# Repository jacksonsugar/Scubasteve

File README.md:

# Scubasteve
Files and notes for AUV development

Microstrain driver

http://wiki.ros.org/microstrain_3dm_gx5_45

https://github.com/sjphilli/microstrain_3dm_gx5_45

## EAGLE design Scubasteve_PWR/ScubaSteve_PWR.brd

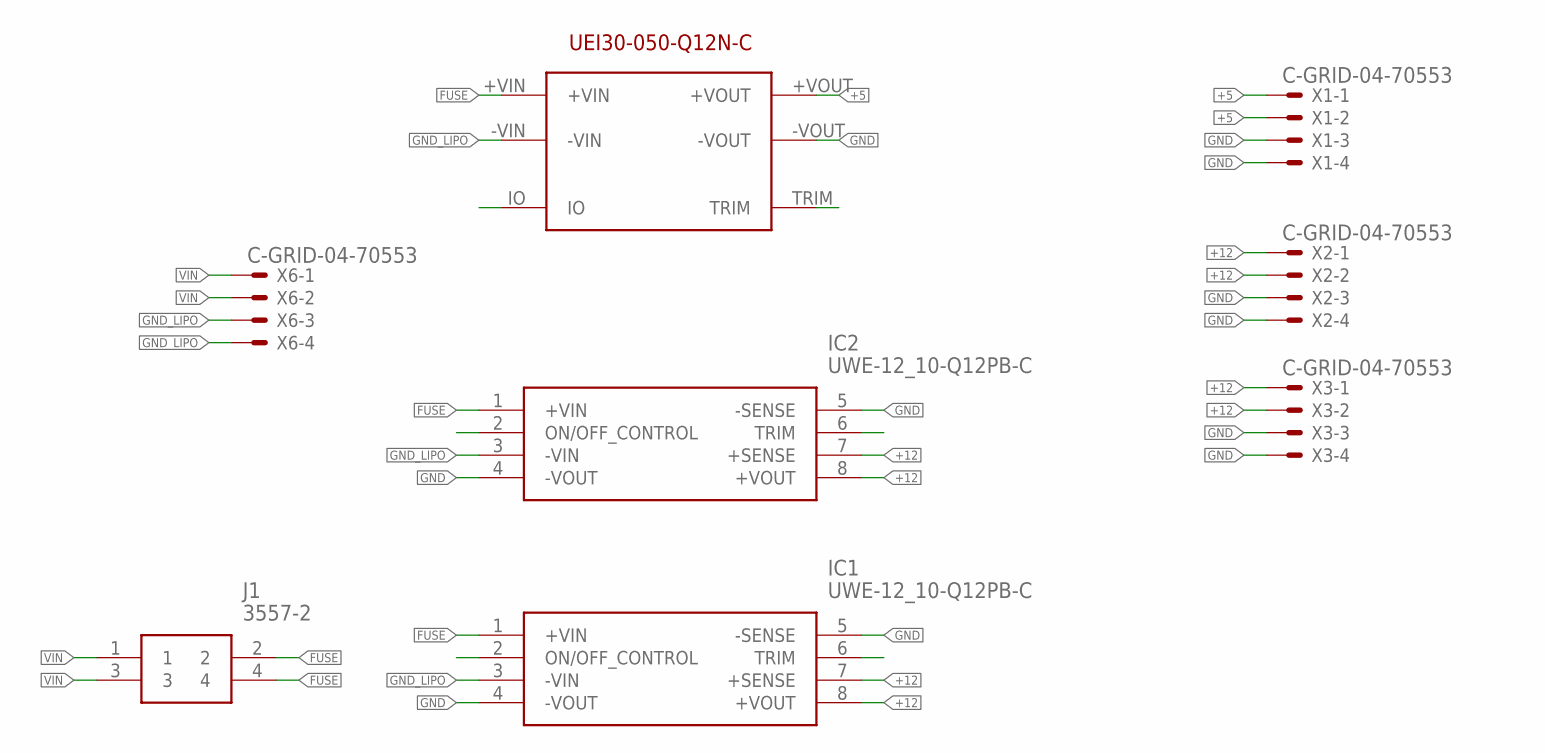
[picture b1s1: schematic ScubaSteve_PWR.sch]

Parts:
IC1, IC2: UWE-12_10-Q12PB-C; UWE520Q48NC
J1: 3557-2
U$1: UEI30-050-Q12N-C
X1, X2, X3, X6: C-GRID-04-70553; 70553-04

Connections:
+5: U$1.+VOUT, X1.1, X1.2
+12: IC1.7 (+SENSE), IC1.8 (+VOUT), IC2.7 (+SENSE), IC2.8 (+VOUT), X2.1, X2.2, X3.1, X3.2
FUSE: IC1.1 (+VIN), IC2.1 (+VIN), J1.2, J1.4, U$1.+VIN
GND: IC1.4 (-VOUT), IC1.5 (-SENSE), IC2.4 (-VOUT), IC2.5 (-SENSE), U$1.-VOUT, X1.3, X1.4, X2.3, X2.4, X3.3, X3.4
GND_LIPO: IC1.3 (-VIN), IC2.3 (-VIN), U$1.-VIN, X6.3, X6.4
VIN: J1.1, J1.3, X6.1, X6.2

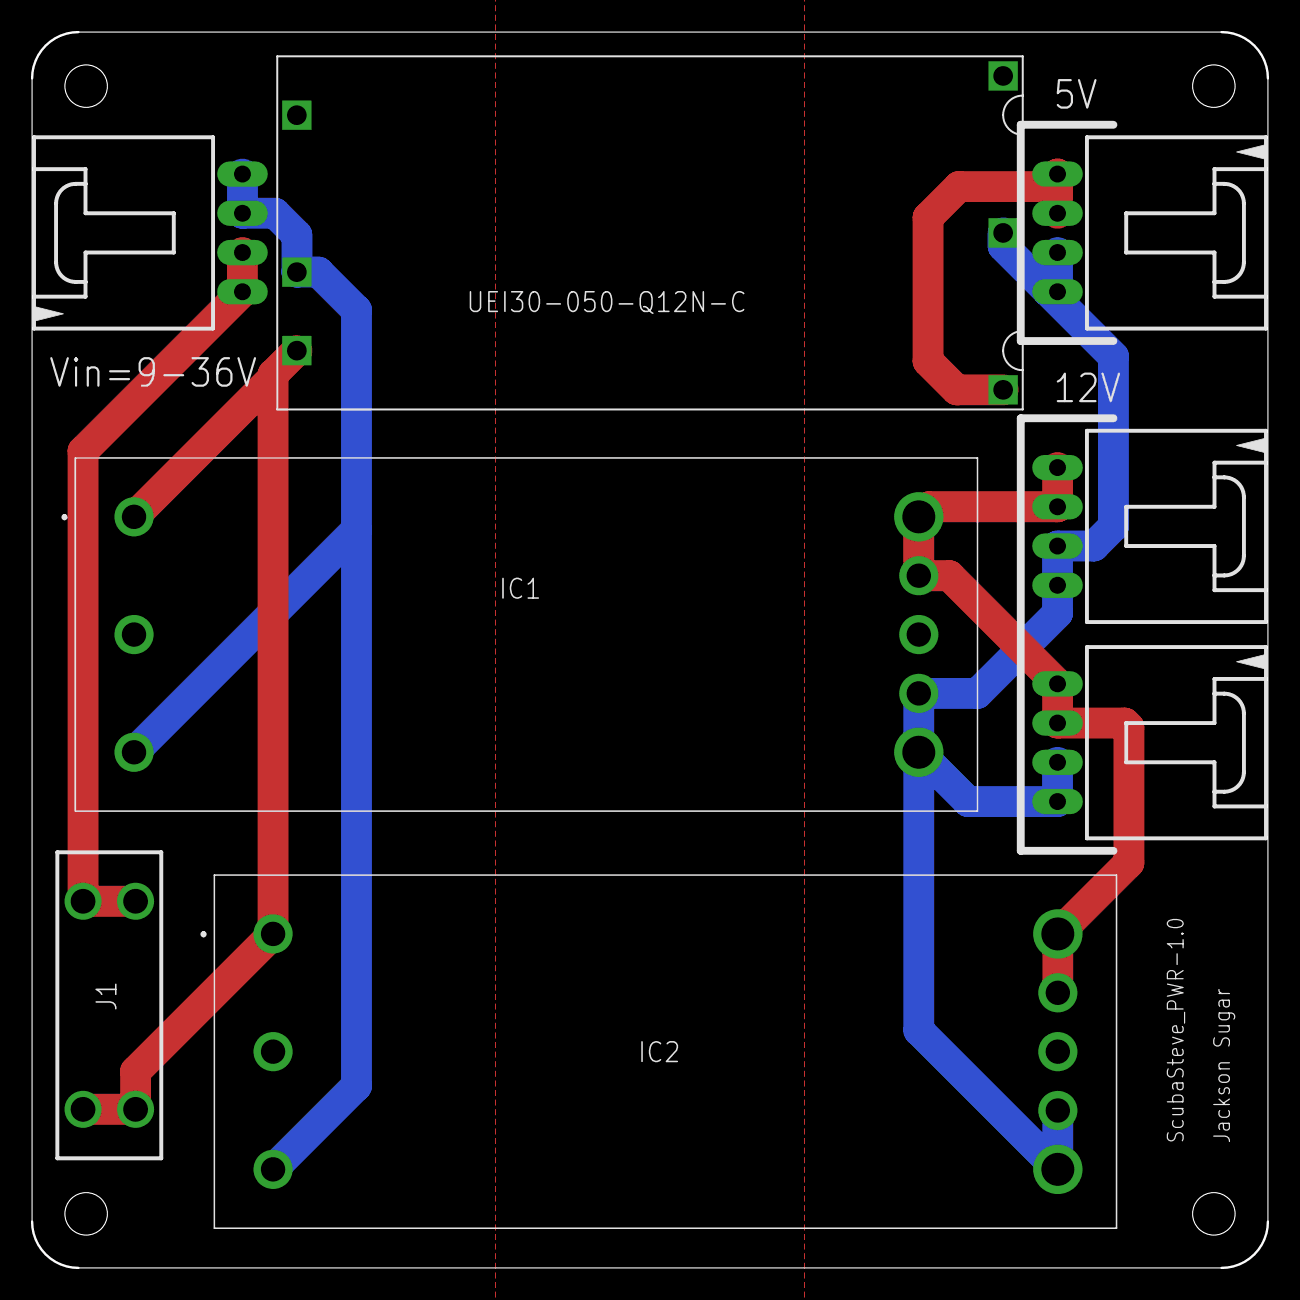
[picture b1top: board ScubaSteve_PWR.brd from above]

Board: 2 copper layers, 80.0 x 80.0 mm, 8 parts (0 on the bottom side), 6 nets.

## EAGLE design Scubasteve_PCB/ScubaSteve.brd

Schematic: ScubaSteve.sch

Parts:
+5: C0805T105K4RACTU; CAPC2012X100N
C1, C2, C3, C4, C5, C7: C0805T105K4RACTU; CAPC2012X100N
C6: 0.1uF; CAP_0805
D1, D2, D3, D4, D5, D6, D7, D8, D9, D10, D11, D12, D13, D14, D15, D16, D17, D18, D19, D20, D21, D22, D23, D24, D25, D26, D27, D28, D29, D30, D31, D32: CMF01(TE12L,Q,M); SODFL4724X108N
GND: SI4946CDY-T1-GE3; SOIC127P600X175-8N
IC1: ATMEGA2560-16AU; QFP50P1600X1600X120-100N
IC2: ADS1115; SOP50P490X110-10N
IC3, IC6, IC7, IC8: L298P; SOIC127P1420X360-21N
IC4, IC5: TMP36GRTZ-REEL7; SOT95P280X145-5N
IC9: DS3231/SO; SO16W
ISP1: AVRISP-6; AVRISP
J1: 2-826942-0; HDRV40W63P254_2X20_5080X500X88
JP1, JP2, JP3: PINHD-1X3; 1X03
Q1: SI4946CDY-T1-GE3; SOIC127P600X175-8N
Q3: CRYSTALHC49S; HC49/S
R1, R2, R3, R8, R9, R10, R11: 10k; 0603
U$1, U$4: DF13-4P-1.25H; DF13A-4P-1.25H
U$3: NEOPIXEL_12_FOOTPRINT
U$11: CR1220_HOLDER
U$12: KMR621NGLFS
X1, X2, X3, X4, X5, X6: C-GRID-04-70553; 70553-04

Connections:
+3: J1.17
+5: +5.1, C6.1, IC1.10 (VCC), IC1.31 (VCC_1), IC1.61 (VCC_2), IC1.80 (VCC_3), IC1.98 (AREF), IC1.100 (AVCC), IC2.4 (AIN0), IC2.8 (VDD), IC4.2 (+VS), IC5.2 (+VS), IC9.2 (VCC), ISP1.2 (VCC), J1.2, J1.4, JP1.2, JP2.2, JP3.2, R1.1, R2.2, R3.2, U$1.P$1 (1), U$3.5V, U$4.P$1 (1)
+12: C1.1, C2.1, C3.1, C5.1, D1.1 (K), D2.1 (K), D3.1 (K), D4.1 (K), D9.1 (K), D10.1 (K), D11.1 (K), D12.1 (K), D17.1 (K), D18.1 (K), D19.1 (K), D20.1 (K), D25.1 (K), D26.1 (K), D27.1 (K), D28.1 (K), IC3.6 (VS), IC3.12 (VSS), IC6.6 (VS), IC6.12 (VSS), IC7.6 (VS), IC7.12 (VSS), IC8.6 (VS), IC8.12 (VSS), X6.1, X6.2
D23: IC1.77 (PA1_[AD1]), IC7.9 (INPUT2)
D24: IC1.76 (PA2_[AD2]), IC7.7 (INPUT1)
D25: IC1.75 (PA3_[AD3]), IC6.13 (INPUT3)
D26: IC1.74 (PA4_[AD4]), IC6.15 (INPUT4)
D27: IC1.73 (PA5_[AD5]), IC6.7 (INPUT1)
D28: IC1.72 (PA6_[AD6]), IC6.9 (INPUT2)
D29: IC1.71 (PA7_[AD7]), IC7.15 (INPUT4)
D32: IC1.58 (PC5_[A13]), IC8.9 (INPUT2)
D33: IC1.57 (PC4_[A12]), IC8.7 (INPUT1)
D34: IC1.56 (PC3_[A11]), IC3.15 (INPUT4)
D35: IC1.55 (PC2_[A10]), IC3.13 (INPUT3)
D36: IC1.54 (PC1_[A9]), IC3.7 (INPUT1)
D37: IC1.53 (PC0_[A8]), IC3.9 (INPUT2)
D39: IC1.70 (PG2_[ALE]), IC7.13 (INPUT3)
D40: IC1.52 (PG1_[!RD]), IC8.15 (INPUT4)
D41: IC1.51 (PG0_[!WR]), IC8.13 (INPUT3)
DRAIN1: Q1.7 (D1_1), Q1.8 (D1_2), X1.1
DRAIN2: Q1.5 (D2_1), Q1.6 (D2_2), X1.2
DRAIN3: GND.7 (D1_1), GND.8 (D1_2), X1.3
DRAIN4: GND.5 (D2_1), GND.6 (D2_2), X1.4
GATE1: IC1.41 (PL6), Q1.2 (G1), R8.1
GATE2: IC1.37 ([T5]_PL2)
GATE3: IC1.36 ([ICP5]_PL1)
GATE4: IC1.35 ([ICP4]_PL0)
GND: +5.2, C1.2, C2.2, C3.2, C4.2, C5.2, C6.2, C7.2, D5.2 (A), D6.2 (A), D7.2 (A), D8.2 (A), D13.2 (A), D14.2 (A), D15.2 (A), D16.2 (A), D21.2 (A), D22.2 (A), D23.2 (A), D24.2 (A), D29.2 (A), D30.2 (A), D31.2 (A), D32.2 (A), GND.1 (S1), GND.3 (S2), IC1.11 (GND), IC1.32 (GND_1), IC1.62 (GND_2), IC1.81 (GND_3), IC1.99 (GND_4), IC2.3 (GND), IC3.1 (GND), IC3.2 (SENSE_A), IC3.10 (GND_1), IC3.11 (GND_2), IC3.19 (SENSE_B), IC3.20 (GND_3), IC4.5 (GND), IC5.5 (GND), IC6.1 (GND), IC6.2 (SENSE_A), IC6.10 (GND_1), IC6.11 (GND_2), IC6.19 (SENSE_B), IC6.20 (GND_3), IC7.1 (GND), IC7.2 (SENSE_A), IC7.10 (GND_1), IC7.11 (GND_2), IC7.19 (SENSE_B), IC7.20 (GND_3), IC8.1 (GND), IC8.2 (SENSE_A), IC8.10 (GND_1), IC8.11 (GND_2), IC8.19 (SENSE_B), IC8.20 (GND_3), IC9.5 (NC), IC9.6 (NC1), IC9.7 (NC2), IC9.8 (NC3), IC9.9 (NC4), IC9.10 (NC5), IC9.11 (NC6), IC9.12 (NC7), IC9.13 (GND), ISP1.6 (GND), J1.6, J1.39, JP1.3, JP2.3, JP3.3, Q1.1 (S1), Q1.3 (S2), R8.2, R9.2, R10.2, R11.2, U$1.P$4 (4), U$3.GND, U$4.P$4 (4), U$11.-, U$12.3, X6.3, X6.4
MISO: IC1.22 ([MISO/PCINT3]_PB3), ISP1.1 (MISO)
MOSI: IC1.21 ([MOSI/PCINT2]_PB2), ISP1.4 (MOSI)
unnamed: C4.1, IC1.33 (XTAL2), Q3.1
unnamed: C7.1, IC1.34 (XTAL1), Q3.2
OUT_1: D12.2 (A), D16.1 (K), IC7.4 (OUT1), X2.4
OUT_2: D11.2 (A), D15.1 (K), IC7.5 (OUT2), X2.3
OUT_3: D10.2 (A), D14.1 (K), IC7.16 (OUT3), X5.2
OUT_4: D9.2 (A), D13.1 (K), IC7.17 (OUT4), X5.1
OUT_5: D4.2 (A), D8.1 (K), IC8.4 (OUT1), X3.4
OUT_6: D3.2 (A), D7.1 (K), IC8.5 (OUT2), X3.3
OUT_7: D2.2 (A), D6.1 (K), IC8.16 (OUT3), X4.2
OUT_8: D1.2 (A), D5.1 (K), IC8.17 (OUT4), X4.1
OUT_9: D20.2 (A), D24.1 (K), IC3.4 (OUT1), X4.3
OUT_10: D19.2 (A), D23.1 (K), IC3.5 (OUT2), X4.4
OUT_11: D17.2 (A), D21.1 (K), IC3.17 (OUT4), X3.2
OUT_12: D18.2 (A), D22.1 (K), IC3.16 (OUT3), X3.1
OUT_13: D28.2 (A), D32.1 (K), IC6.4 (OUT1), X5.3
OUT_14: D27.2 (A), D31.1 (K), IC6.5 (OUT2), X5.4
OUT_15: D25.2 (A), D29.1 (K), IC6.17 (OUT4), X2.2
OUT_16: D26.2 (A), D30.1 (K), IC6.16 (OUT3), X2.1
PI_RX: IC1.3 ([TXD0]_PE1), J1.10
PI_TX: IC1.2 ([RXD0/PCINT8]_PE0), J1.8
PWM2: IC1.6 ([OC3B/INT4]_PE4), IC3.8 (ENABLE_A)
PWM3: IC1.7 ([OC3C/INT5]_PE5), IC3.14 (ENABLE_B)
PWM4: IC1.1 ([OC0B]_PG5), IC6.14 (ENABLE_B)
PWM5: IC1.5 ([OC3A/AIN1]_PE3), IC6.8 (ENABLE_A)
PWM6: IC1.15 ([OC4A]_PH3), IC7.8 (ENABLE_A)
PWM7: IC1.16 ([OC4B]_PH4), IC7.14 (ENABLE_B)
PWM8: IC1.17 ([OC4C]_PH5), IC8.8 (ENABLE_A)
PWM9: IC1.18 ([OC2B]_PH6), IC8.14 (ENABLE_B)
PWM10: IC1.23 ([OC2A/PCINT4]_PB4), JP3.1
PWM11: IC1.24 ([OC1A/PCINT5]_PB5), JP2.1
PWM12: IC1.25 ([OC1B/PCINT6]_PB6), JP1.1
PWM13: IC1.26 ([OC0A/OC1C/PCINT7]_PB7), U$3.IN
PWM44: IC1.40 ([OC5C]_PL5), Q1.4 (G2), R9.1
PWM45: GND.2 (G1), IC1.39 ([OC5B]_PL4), R10.1
PWM46: GND.4 (G2), IC1.38 ([OC5A]_PL3), R11.1
RESET: IC1.30 (!RESET), ISP1.5 (RST), R1.2, U$12.2
SCK: IC1.20 ([SCK/PCINT1]_PB1), ISP1.3 (SCK)
SCL: IC2.10 (SCL), IC9.16 (SCL), J1.5, R3.1, U$1.P$2 (2), U$4.P$2 (2)
SDA: IC2.9 (SDA), IC9.15 (SDA), J1.3, R2.1, U$1.P$3 (3), U$4.P$3 (3)
T1: IC2.7 (AIN3), IC4.1 (VOUT)
T2: IC2.5 (AIN1), IC5.1 (VOUT)
VBAT: IC9.14 (VBAT), U$11.+, U$11.+1

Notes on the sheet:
AVR ICSP
i2c Pullup
Servo Breakout
DF-13 i2c
LM298 DC Motor Drivers
ATMEGA2560
Mosfet array
JETSON_NANO
INTERNAL ENV
Neopixel
12V IN
RTC

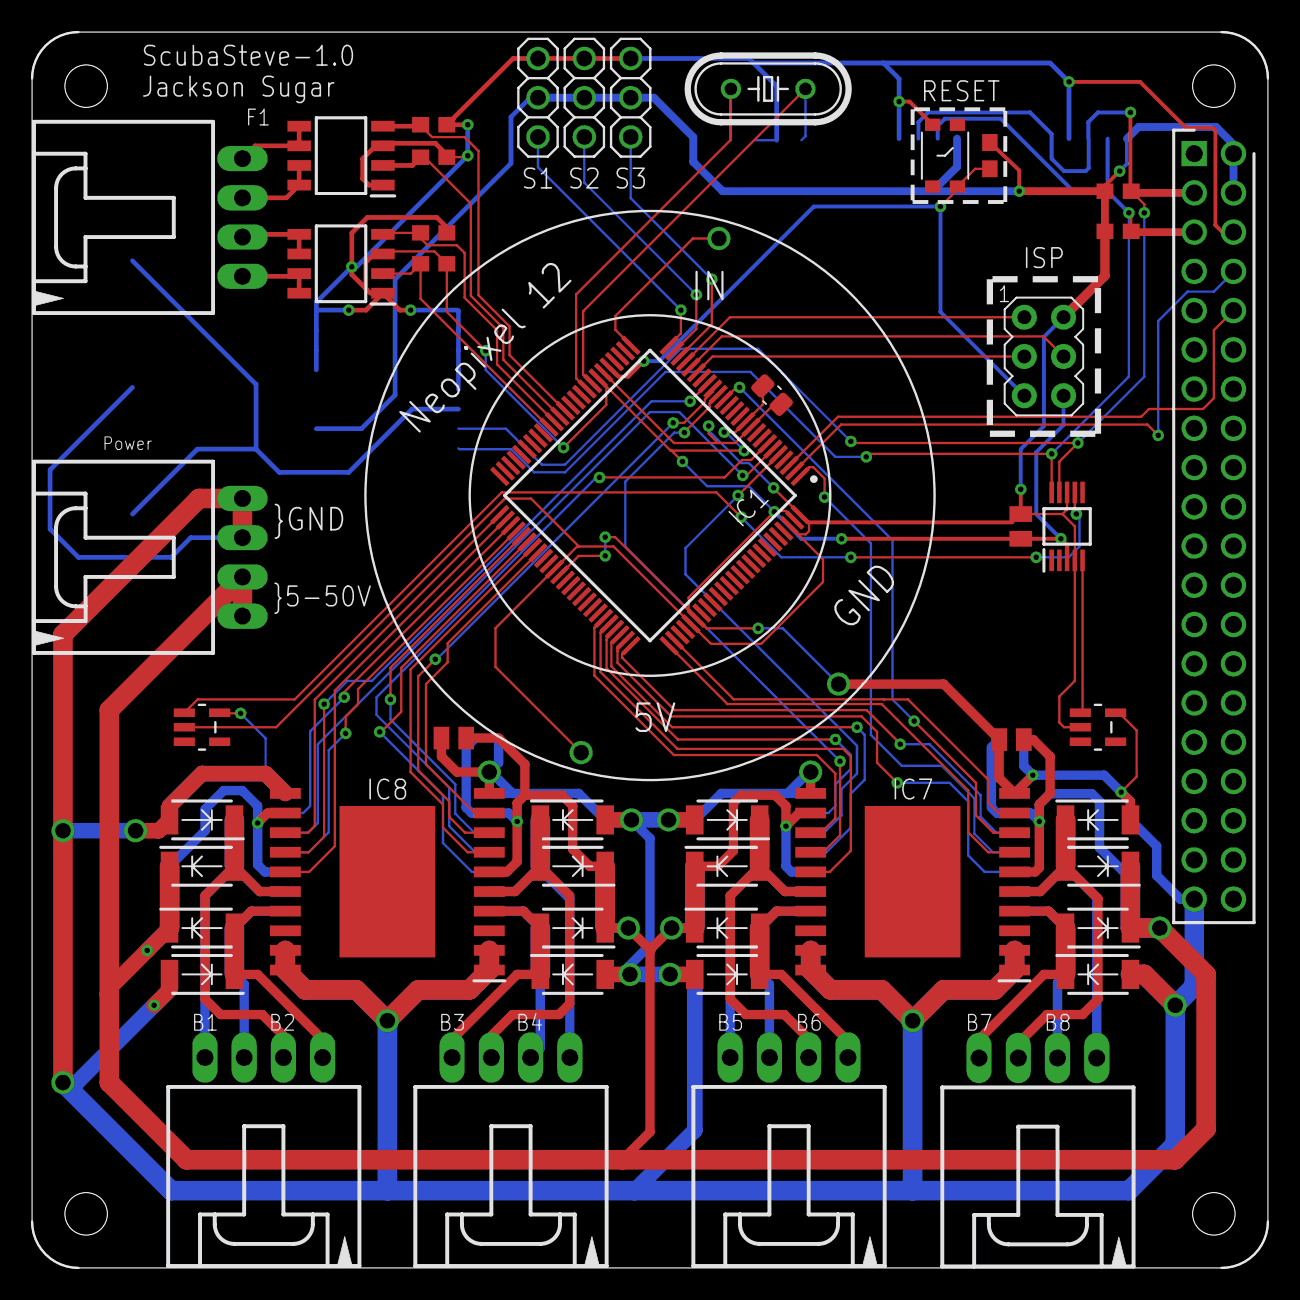
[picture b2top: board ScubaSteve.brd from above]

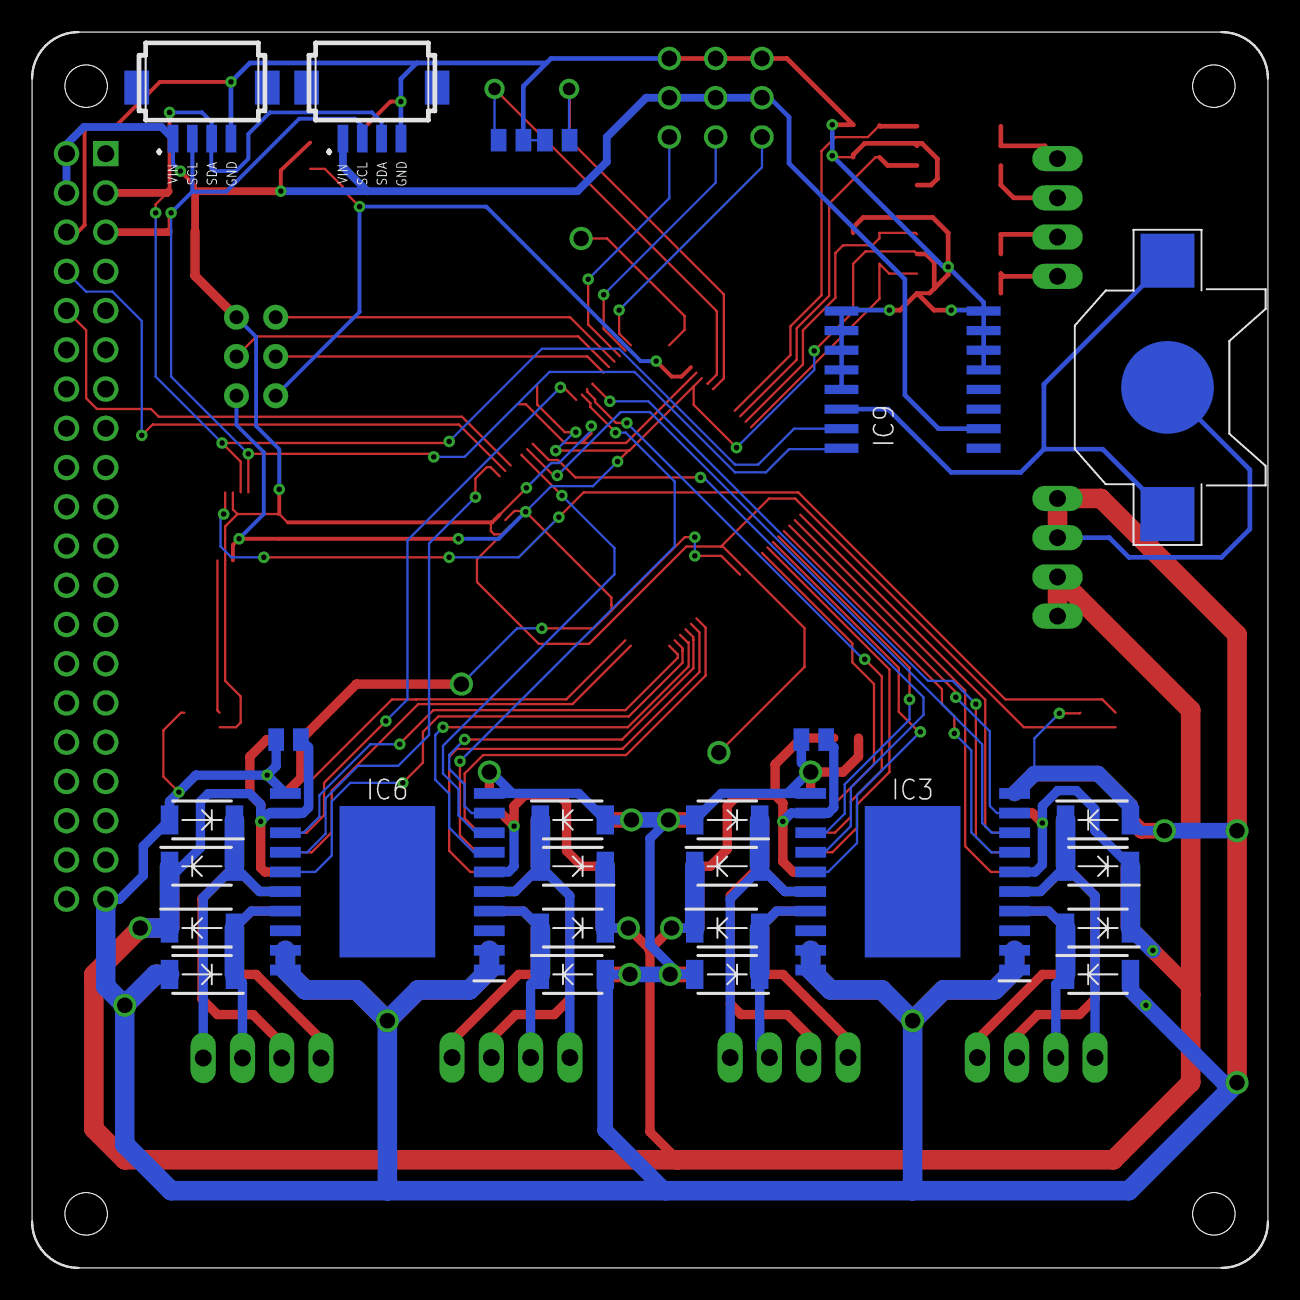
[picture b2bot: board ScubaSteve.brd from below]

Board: 2 copper layers, 80.0 x 80.0 mm, 75 parts (26 on the bottom side), 68 nets.

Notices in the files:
parts and their libraries:
SparkFun-Resistors: Licensing: Creative Commons ShareAlike 4.0 International - https://creativecommons.org/licenses/by-sa/4.0
